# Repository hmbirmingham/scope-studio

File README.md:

# Scope Studio

A backend that stores engineering context as a graph and returns a small,
relevant slice of it for a question. I started it because I was tired of
re-explaining my projects to AI tools at the start of every session.

**Studio:** Fourier Studios
**Status:** Backend retrieval v1. No working frontend, no model routing, no
benchmark results.

## What exists

All of it is in `server/`, written in September 2026.

- **A graph store on PostgreSQL with pgvector.** Nodes have a type (repo, file,
  decision, spec, paper, datasheet, conversation), a 768-dimension embedding
  under an HNSW index, and typed relationships to other nodes: `depends_on`,
  `references`, `supersedes`, `caused_by`, `part_of`.
- **Hybrid retrieval.** A dense search over the embeddings and a lexical search
  over a `tsvector` column, merged with Reciprocal Rank Fusion.
- **Scoring.** Recency decay per node type, a boost for the active project, a
  task-type boost from a centroid classifier, and demotion of any node that a
  newer one supersedes.
- **Graph expansion.** One forward hop from the top-scoring results, so a
  related node can be returned even when it does not match the query text.
- **Token-budget packing.** Each node stores an estimated token length, its
  character count divided by four, and results are packed greedily into a
  budget. The default tier allows 1,500 estimated tokens and 5 nodes.
- **GitHub ingestion over OAuth.** After the OAuth flow it lists the signed-in
  user's repositories and stores one node per repository, holding the name and
  description, with incremental sync by update time.
- **Query metrics.** Each query logs its latency, the tokens it returned, the
  tokens available in the store, and which nodes were chosen. A feedback route
  marks a result as useful.
- **Accounts.** Session auth with hashed passwords.

Embeddings come from `nomic-embed-text` running in Ollama. Nodes other than
repositories, and every relationship, are created through the `/api/nodes`
routes.

## What does not exist

- **A frontend.** `client/` is a React and Vite chat shell that keeps messages
  in local state. It does not call the backend.
- **Model routing.** Nothing here calls a language model. The backend returns
  context and stops. The two retrieval tiers, local and cloud, are parameter
  sets for retrieval. The metrics table has routing columns and nothing writes
  to them.
- **Benchmark results.** There is a `benchmark_runs` table and a benchmark plan
  in `ARCHITECTURE.md`. No benchmark has been run.
- **GitHub file ingestion.** Repository names and descriptions are pulled in.
  File contents are not.
- **Automated tests and CI.**

## What has not been measured

Any efficiency number. The backend computes tokens returned against tokens
available for each query, but I have not run it over a query set. I make no
claim here about token savings, latency or answer quality.

`ARCHITECTURE.md` records the design and the reasoning behind it. Its targets,
such as the token reduction and the 300 ms retrieval budget, are design targets
and are labeled there as unmeasured.

## Repository history

The pull request history goes further than `main`. Between September and
November 2026 I built a much larger version on a separate branch: agents,
model routing, a web interface and more. I set it aside and did not merge it
here. When I made this repository public I deleted those branches, so `main`,
`dev` and `test` hold only what this README describes. The merged pull
requests still show that work, but none of it is on `main`, and nothing in
this README depends on it.

## Stack

- **Backend:** Node.js and Express
- **Database:** PostgreSQL with pgvector
- **Embeddings:** `nomic-embed-text` through Ollama
- **Client shell:** React and Vite, not connected to the backend

## Project structure

| Path | Contents |
|---|---|
| `server/` | The backend: routes, retrieval, the GitHub plugin, migrations |
| `client/` | The unconnected chat shell |
| `ARCHITECTURE.md` | Design decisions and the benchmark plan |

## Setup

1. Copy `.env.example` to `server/.env` and fill in the required values.
2. Run `npm install` in `server/`.
3. Run `npm run migrate` to create the schema. PostgreSQL needs the pgvector
   extension available.
4. Run `npm run dev` to start the server.

`npm run embed` backfills embeddings for nodes that were created while Ollama
was unreachable, and `npm run centroids` builds the task-type centroids.

## License

MIT, see [LICENSE](LICENSE).

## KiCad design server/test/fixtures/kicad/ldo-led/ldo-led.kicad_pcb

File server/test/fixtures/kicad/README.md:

# KiCad test fixtures

Written for Scope Studio's KiCad plug-in tests and released under CC0 1.0
(public domain dedication). Nothing here is copied from KiCad's libraries or
from any other project; the library symbols embedded in the schematics are
simplified drawings that only borrow KiCad's well-known library names
(`Device:R`, `power:GND`, …) so the files read like ordinary KiCad projects.

- `ldo-led/` — a KiCad 8 project: a 2-pin input connector feeding an
  AMS1117-3.3 LDO regulator with 10 µF input and 22 µF output capacitors, and
  a red LED with a 330 Ω series resistor on the 3.3 V rail.
  `ldo-led.kicad_sch` is the schematic, `ldo-led.kicad_pcb` the board (parts
  placed and every pad on its net, not routed), `ldo-led.kicad_pro` the
  project file.
- `ldo-led-faulty/` — the same schematic with deliberate faults for the
  review: the output capacitor removed (the 3.3 V rail has no decoupling),
  R1's value cleared, D1's footprint cleared, D1's cathode left unconnected,
  and a test point with a no-connect flag (which must not be reported).
- `reports/` — ERC and DRC reports in the JSON format kicad-cli 8 writes
  (`schemas.kicad.org/erc.v1.json` and `drc.v1.json`). They were written by
  hand for these fixtures, not captured from kicad-cli: kicad-cli 8 was not
  installable where the plug-in was built (Ubuntu 24.04 ships KiCad 7, whose
  kicad-cli has no `erc`/`drc` commands). Tests use them to exercise the
  verifiers when kicad-cli is absent; where kicad-cli 8+ is installed the
  tests also run the real tool on the fixtures.

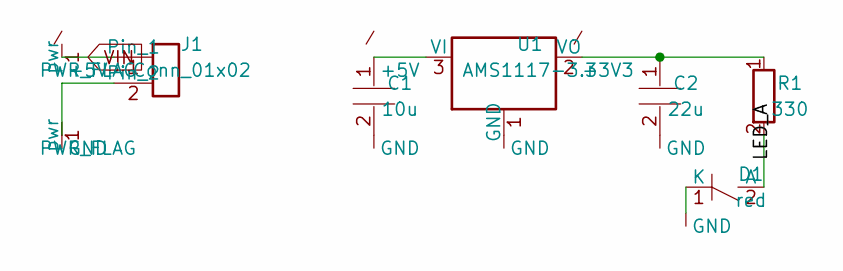
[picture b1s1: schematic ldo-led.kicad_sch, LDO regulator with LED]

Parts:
C1: 10u; C_0805_2012Metric
C2: 22u; C_0805_2012Metric
D1: red; LED_0603_1608Metric
J1: Conn_01x02; PinHeader_1x02_P2.54mm_Vertical
R1: 330; R_0603_1608Metric
U1: AMS1117-3.3; SOT-223-3_TabPin2

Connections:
+3V3: C2.1, R1.1, U1.2 (VO)
+5V: C1.1, J1.1, U1.3 (VI)
/LED_A: D1.2 (A), R1.2
GND: C1.2, C2.2, D1.1 (K), J1.2, U1.1 (GND)

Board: 2 copper layers, 6 parts (1 on the bottom side), 4 nets, no tracks yet.
